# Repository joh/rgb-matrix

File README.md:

# RGB Matrix

RGB Matrix is a driver board for 8x8 RGB matrix displays.

## Features
* USB: The display is controlled over USB.
* 48-bit: Each RGB channel is 16 bits, meaning true 48-bit color!
* Tileable: Multiple displays can be tiled to form bigger displays.
* CA/CC: Both Common Anode and Common Cathode displays are supported.
* Power options: The display can either be powered by USB or via an external
  power adapter.

## Tiling
Several boards can be tiled together to create larger displays. Frames are
propagated to each board over SPI in a daisy chain configuration.

More exotic configurations are also possible:

## 48-bit color
Each color channel is 16 bits which means true 48-bit color per pixel.
That's more than 281 *trillion* colors!
With such a high color depth, transitions between colors appears seamless,
resulting in beautiful smooth animations.

## Hardware
For details about the hardware, head over to [hardware/README.md](hardware/README.md)

## Firmware
TBD

## Client
TBD

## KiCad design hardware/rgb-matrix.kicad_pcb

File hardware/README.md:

# Hardware
The board is based around an STM32F405 microcontroller which drives each LED
with 16-bit hardware PWM. It also handles USB, SPI, etc.

Each column is driven by SN74AC244 buffers, while the rows are driven by
TBD62783 (common anode) or TBD62083/ULN2803A (common cathode).

## PCB
The PCB is 4 layers and connects with the LED matrix like a backpack.

The PCB was designed to handle currents up to 6A, which typically means max 8
panels in series, with the limiting component being the pin headers.

## BOM
TODO

## Assembly
TODO: Some tips on soldering the board

## Common cathode / common anode
TODO: info on components for CA/CC + jumpers

## Power options
TODO: info about the jumpers

## Tiling
TODO: how to set jumpers

## Supported RGB displays
The board was originally designed for the 8x8 RGB Matrix sold by SparkFun (now
sadly discontinued). Luckily there are plenty of displays on the market which
are pin compatible. Some of them are listed below.

Any display with the same form factor should work, *as long as the rows are on
pins 7-10 and 23-26*. Exactly which rows and columns are where is less
important: they can be easily remapped in firmware.

TODO: picture

If you find a display that looks compatible which is not in the list below,
please let me know so I can add it!

Tested displays:
* [YSM-2388CRGBC](https://www.sparkfun.com/products/retired/683) (common cathode, retired)
* [ARK-SZ912388RGB](https://wxjsinfo.en.alibaba.com/product/1877395129-801004755/8x8_RGB_led_matrix_with_7_62mm_pitch.html) (common anode)

Should work:
* [Betlux BL-M23B881RGB-11](http://shop.evilmadscientist.com/productsmenu/241) (common cathode)
* [LEDM88RGBCC](http://www.futurlec.com/LED/LEDM88RGBCC.shtml) (common cathode)

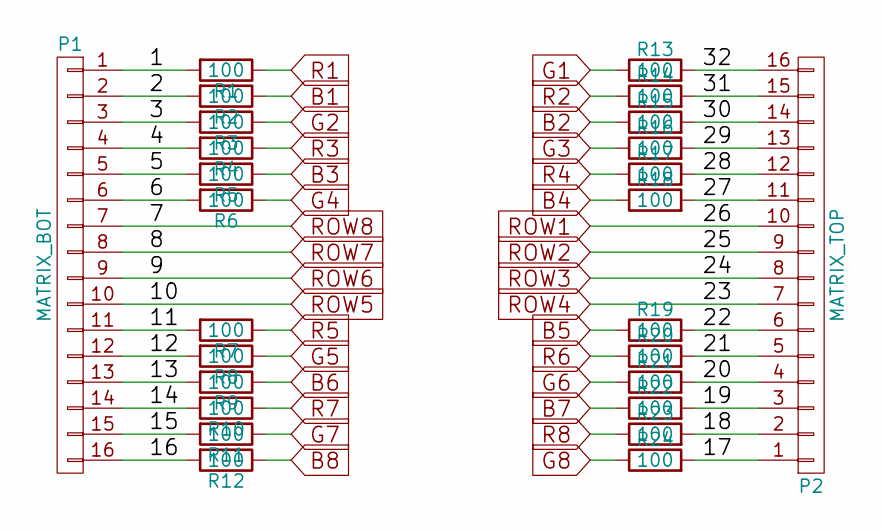
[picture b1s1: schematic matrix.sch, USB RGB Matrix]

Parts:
P1: MATRIX_BOT; Socket_Strip_Straight_1x16
P2: MATRIX_TOP; Socket_Strip_Straight_1x16
R1, R2, R3, R4, R5, R6, R7, R8, R9, R10, R11, R12, R13, R14, R15, R16, R17, R18, R19, R20, R21, R22, R23, R24: 100; R_0805

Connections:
/matrix/1: P1.1, R1.2
/matrix/2: P1.2, R2.2
/matrix/3: P1.3, R3.2
/matrix/4: P1.4, R4.2
/matrix/5: P1.5, R5.2
/matrix/6: P1.6, R6.2
/matrix/11: P1.11, R7.2
/matrix/12: P1.12, R8.2
/matrix/13: P1.13, R9.2
/matrix/14: P1.14, R10.2
/matrix/15: P1.15, R11.2
/matrix/16: P1.16, R12.2
/matrix/17: P2.1, R24.2
/matrix/18: P2.2, R23.2
/matrix/19: P2.3, R22.2
/matrix/20: P2.4, R21.2
/matrix/21: P2.5, R20.2
/matrix/22: P2.6, R19.2
/matrix/27: P2.11, R18.2
/matrix/28: P2.12, R17.2
/matrix/29: P2.13, R16.2
/matrix/30: P2.14, R15.2
/matrix/31: P2.15, R14.2
/matrix/32: P2.16, R13.2
B1: R2.1; also elsewhere on the board
B2: R15.1; also elsewhere on the board
B3: R5.1; also elsewhere on the board
B4: R18.1; also elsewhere on the board
B5: R19.1; also elsewhere on the board
B6: R9.1; also elsewhere on the board
B7: R22.1; also elsewhere on the board
B8: R12.1; also elsewhere on the board
G1: R13.1; also elsewhere on the board
G2: R3.1; also elsewhere on the board
G3: R16.1; also elsewhere on the board
G4: R6.1; also elsewhere on the board
G5: R8.1; also elsewhere on the board
G6: R21.1; also elsewhere on the board
G7: R11.1; also elsewhere on the board
G8: R24.1; also elsewhere on the board
R1: R1.1; also elsewhere on the board
R2: R14.1; also elsewhere on the board
R3: R4.1; also elsewhere on the board
R4: R17.1; also elsewhere on the board
R5: R7.1; also elsewhere on the board
R6: R20.1; also elsewhere on the board
R7: R10.1; also elsewhere on the board
R8: R23.1; also elsewhere on the board
ROW1: P2.10; also elsewhere on the board
ROW2: P2.9; also elsewhere on the board
ROW3: P2.8; also elsewhere on the board
ROW4: P2.7; also elsewhere on the board
ROW5: P1.10; also elsewhere on the board
ROW6: P1.9; also elsewhere on the board
ROW7: P1.8; also elsewhere on the board
ROW8: P1.7; also elsewhere on the board

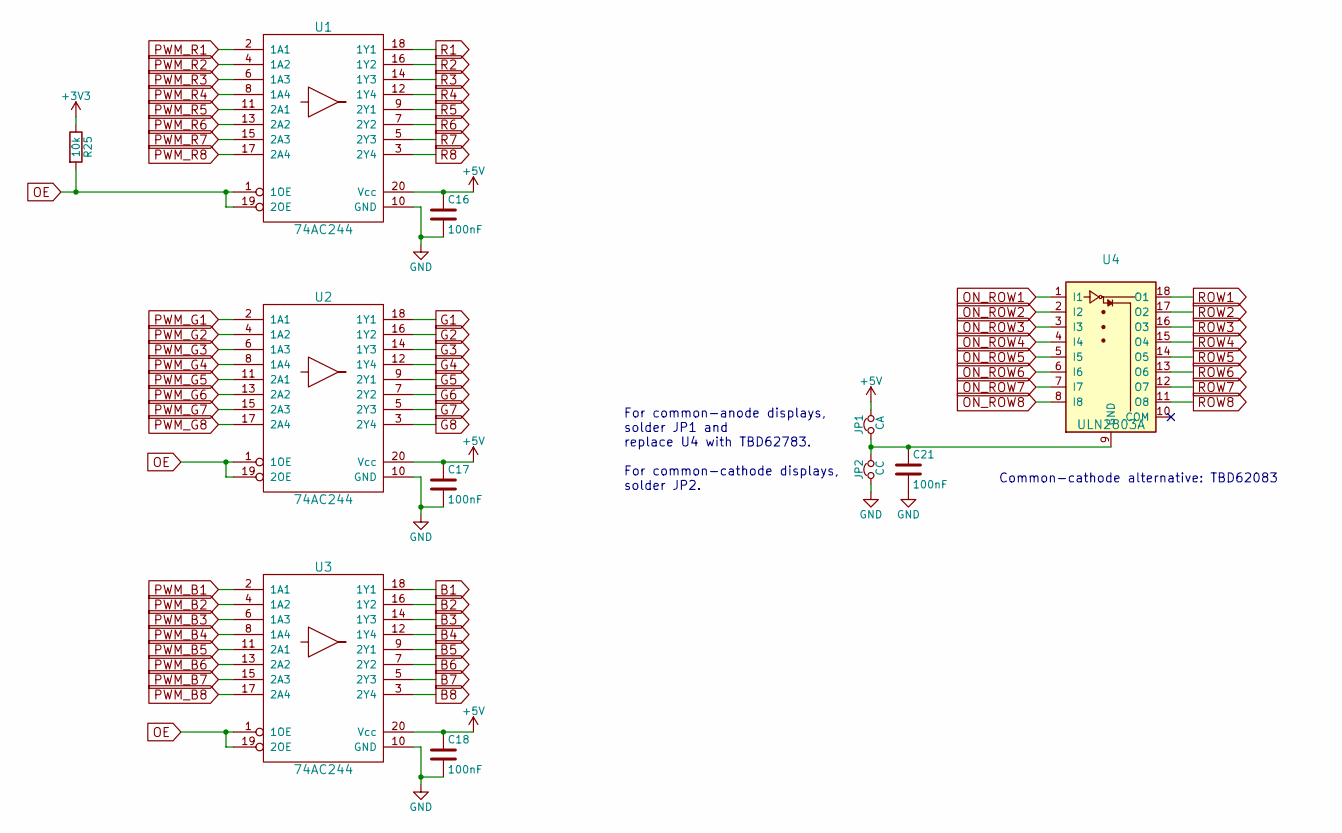
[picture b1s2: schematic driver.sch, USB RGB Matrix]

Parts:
C16, C17, C18, C21: 100nF; C_0805
JP1: CA; SMD-solder-bridge-1mm
JP2: CC; SMD-solder-bridge-1mm
R25: 10k; R_0805
U1, U2, U3: 74AC244; TSSOP-20_4.4x6.5mm_Pitch0.65mm
U4: ULN2803A; SOIC-18W_7.5x11.6mm_Pitch1.27mm

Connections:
+3V3: R25.1; also elsewhere on the board
+5V: C16.1, C17.1, C18.1, JP1.2, U1.20 (Vcc), U2.20 (Vcc), U3.20 (Vcc); also elsewhere on the board
B1: U3.18 (1Y1); also elsewhere on the board
B2: U3.16 (1Y2); also elsewhere on the board
B3: U3.14 (1Y3); also elsewhere on the board
B4: U3.12 (1Y4); also elsewhere on the board
B5: U3.9 (2Y1); also elsewhere on the board
B6: U3.7 (2Y2); also elsewhere on the board
B7: U3.5 (2Y3); also elsewhere on the board
B8: U3.3 (2Y4); also elsewhere on the board
G1: U2.18 (1Y1); also elsewhere on the board
G2: U2.16 (1Y2); also elsewhere on the board
G3: U2.14 (1Y3); also elsewhere on the board
G4: U2.12 (1Y4); also elsewhere on the board
G5: U2.9 (2Y1); also elsewhere on the board
G6: U2.7 (2Y2); also elsewhere on the board
G7: U2.5 (2Y3); also elsewhere on the board
G8: U2.3 (2Y4); also elsewhere on the board
GND: C16.2, C17.2, C18.2, C21.2, JP2.1, U1.10 (GND), U2.10 (GND), U3.10 (GND); also elsewhere on the board
unnamed: C21.1, JP1.1, JP2.2, U4.9 (GND)
OE: R25.2, U1.1 (1OE), U1.19 (2OE), U2.1 (1OE), U2.19 (2OE), U3.1 (1OE), U3.19 (2OE); also elsewhere on the board
ON_ROW1: U4.1 (I1); also elsewhere on the board
ON_ROW2: U4.2 (I2); also elsewhere on the board
ON_ROW3: U4.3 (I3); also elsewhere on the board
ON_ROW4: U4.4 (I4); also elsewhere on the board
ON_ROW5: U4.5 (I5); also elsewhere on the board
ON_ROW6: U4.6 (I6); also elsewhere on the board
ON_ROW7: U4.7 (I7); also elsewhere on the board
ON_ROW8: U4.8 (I8); also elsewhere on the board
PWM_B1: U3.2 (1A1); also elsewhere on the board
PWM_B2: U3.4 (1A2); also elsewhere on the board
PWM_B3: U3.6 (1A3); also elsewhere on the board
PWM_B4: U3.8 (1A4); also elsewhere on the board
PWM_B5: U3.11 (2A1); also elsewhere on the board
PWM_B6: U3.13 (2A2); also elsewhere on the board
PWM_B7: U3.15 (2A3); also elsewhere on the board
PWM_B8: U3.17 (2A4); also elsewhere on the board
PWM_G1: U2.2 (1A1); also elsewhere on the board
PWM_G2: U2.4 (1A2); also elsewhere on the board
PWM_G3: U2.6 (1A3); also elsewhere on the board
PWM_G4: U2.8 (1A4); also elsewhere on the board
PWM_G5: U2.11 (2A1); also elsewhere on the board
PWM_G6: U2.13 (2A2); also elsewhere on the board
PWM_G7: U2.15 (2A3); also elsewhere on the board
PWM_G8: U2.17 (2A4); also elsewhere on the board
PWM_R1: U1.2 (1A1); also elsewhere on the board
PWM_R2: U1.4 (1A2); also elsewhere on the board
PWM_R3: U1.6 (1A3); also elsewhere on the board
PWM_R4: U1.8 (1A4); also elsewhere on the board
PWM_R5: U1.11 (2A1); also elsewhere on the board
PWM_R6: U1.13 (2A2); also elsewhere on the board
PWM_R7: U1.15 (2A3); also elsewhere on the board
PWM_R8: U1.17 (2A4); also elsewhere on the board
R1: U1.18 (1Y1); also elsewhere on the board
R2: U1.16 (1Y2); also elsewhere on the board
R3: U1.14 (1Y3); also elsewhere on the board
R4: U1.12 (1Y4); also elsewhere on the board
R5: U1.9 (2Y1); also elsewhere on the board
R6: U1.7 (2Y2); also elsewhere on the board
R7: U1.5 (2Y3); also elsewhere on the board
R8: U1.3 (2Y4); also elsewhere on the board
ROW1: U4.18 (O1); also elsewhere on the board
ROW2: U4.17 (O2); also elsewhere on the board
ROW3: U4.16 (O3); also elsewhere on the board
ROW4: U4.15 (O4); also elsewhere on the board
ROW5: U4.14 (O5); also elsewhere on the board
ROW6: U4.13 (O6); also elsewhere on the board
ROW7: U4.12 (O7); also elsewhere on the board
ROW8: U4.11 (O8); also elsewhere on the board

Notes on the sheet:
Common-cathode alternative: TBD62083
For common-anode displays, solder JP1 and replace U4 with TBD62783. For common-cathode displays, solder JP2.

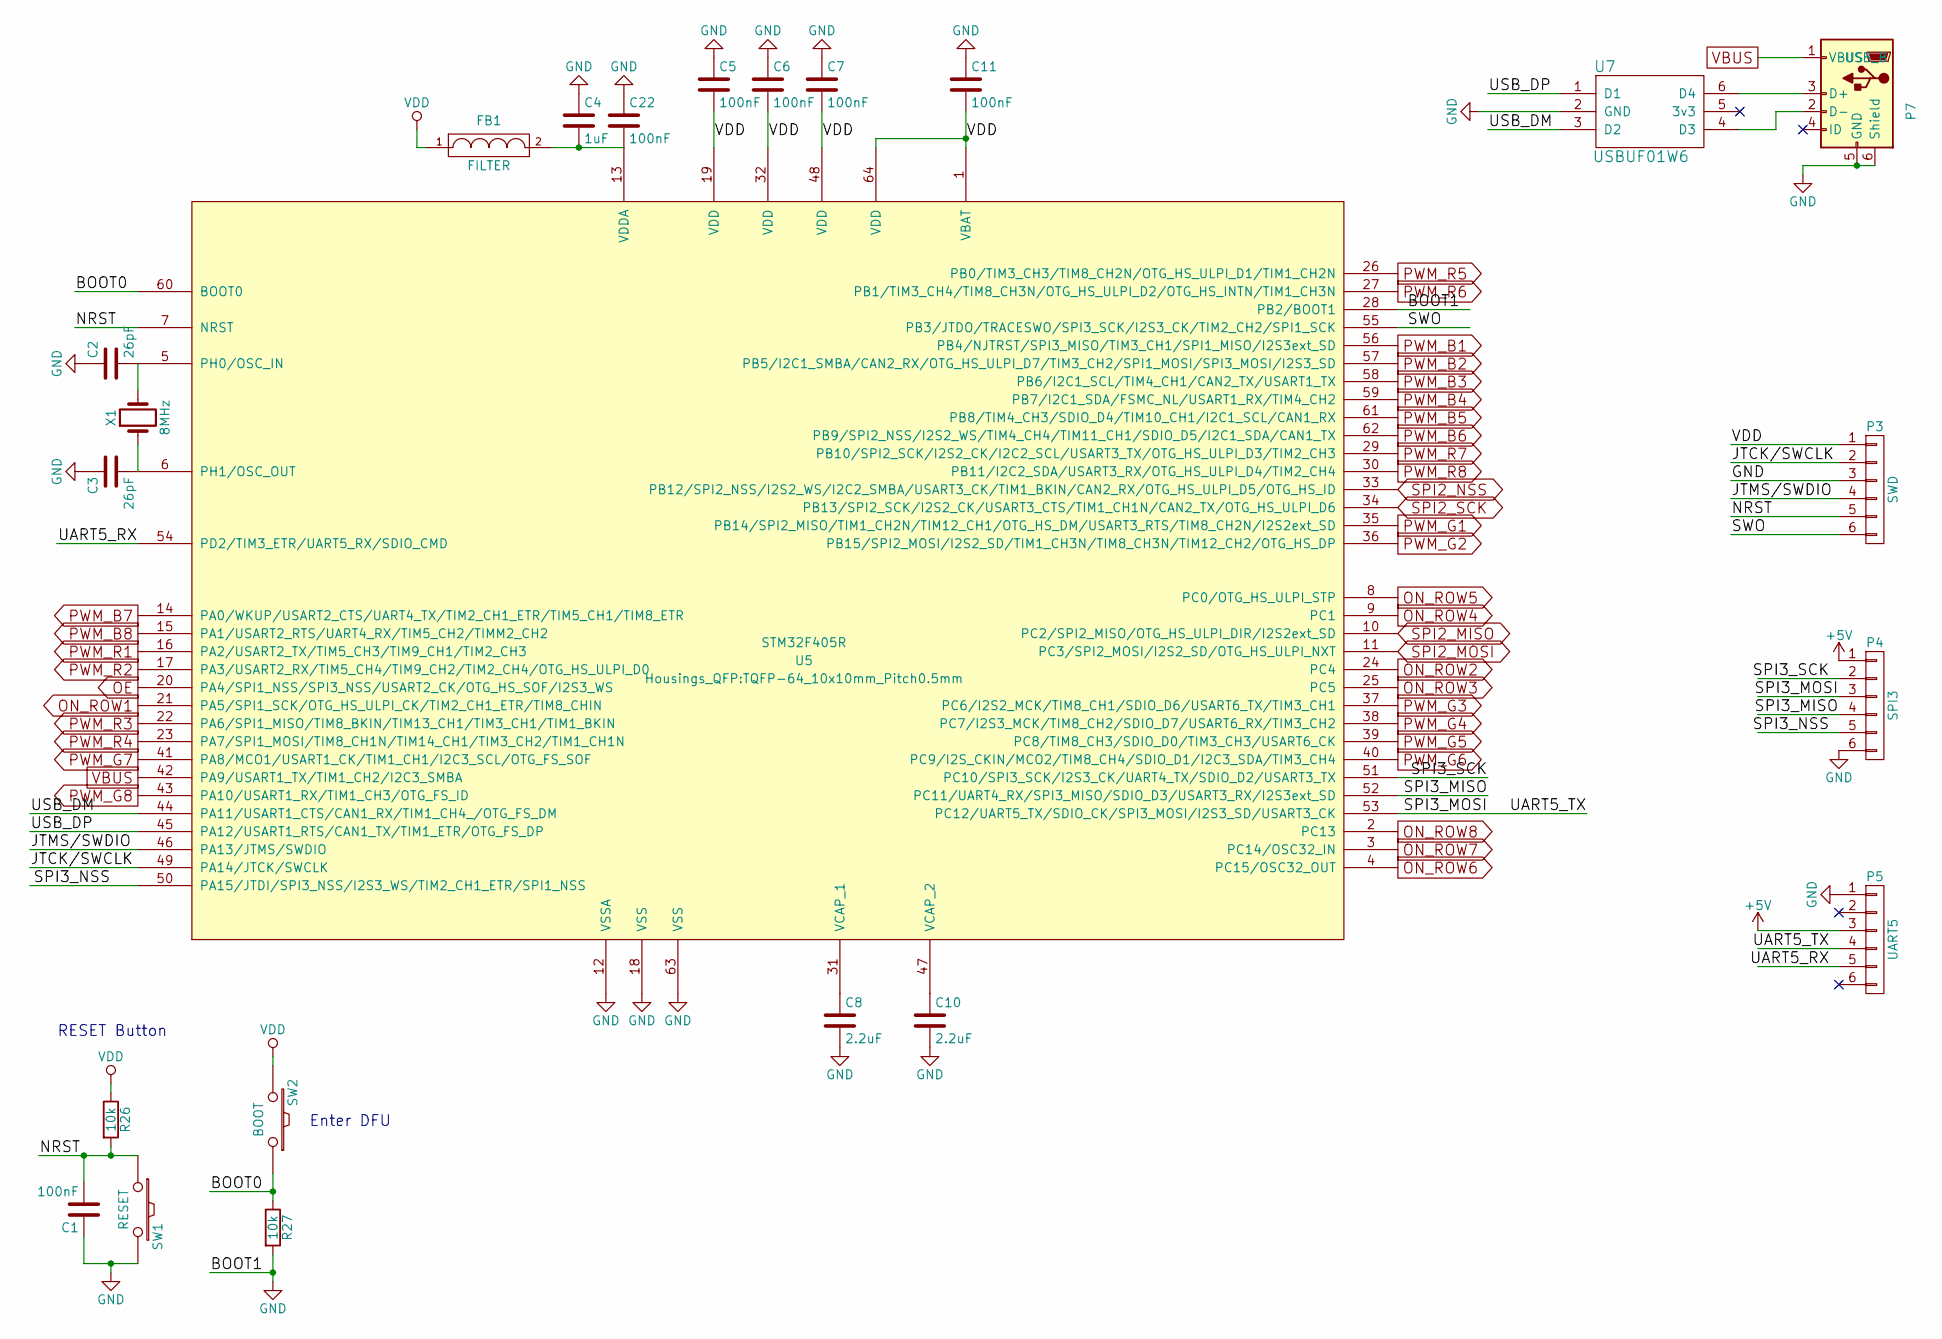
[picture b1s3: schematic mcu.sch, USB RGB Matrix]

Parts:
C1, C5, C6, C7, C11, C22: 100nF; C_0805
C2, C3: 26pF; C_0805
C4: 1uF; C_0805
C8, C10: 2.2uF; C_0805
FB1: FILTER; R_0805
P3: SWD; Pin_Header_Straight_1x06
P4: SPI3; Pin_Header_Straight_1x06
P5: UART5; Pin_Header_Straight_1x06
P7: USB_B; USB_Micro-B
R26, R27: 10k; R_0805
SW1: RESET; SW_SPST_SKQG
SW2: BOOT; SW_SPST_SKQG
U5: STM32F405R; TQFP-64_10x10mm_Pitch0.5mm
U7: USBUF01W6; SOT323-6L
X1: 8MHz; Crystal_SMD_5032_2Pads

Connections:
+3V3: C5.2, C6.2, C7.2, C11.2, FB1.1, P3.1, R26.1, SW2.2, U5.1 (VBAT), U5.19 (VDD), U5.32 (VDD), U5.48 (VDD), U5.64 (VDD); also elsewhere on the board
+5V: P4.1, P5.3; also elsewhere on the board
/mcu/BOOT0: R27.1, SW2.1, U5.60 (BOOT0)
/mcu/JTCK/SWCLK: P3.2, U5.49 (PA14/JTCK/SWCLK)
/mcu/JTMS/SWDIO: P3.4, U5.46 (PA13/JTMS/SWDIO)
/mcu/NRST: C1.2, P3.5, R26.2, SW1.1, U5.7 (NRST)
/mcu/SPI3_MISO: P4.4, U5.52 (PC11/UART4_RX/SPI3_MISO/SDIO_D3/USART3_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)
/mcu/SPI3_MOSI: P4.3, P5.4, U5.53 (PC12/UART5_TX/SDIO_CK/SPI3_MOSI/I2S3_SD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)
/mcu/SPI3_NSS: P4.5, U5.50 (PA15/JTDI/SPI3_NSS/I2S3_WS/TIM2_CH1_ETR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)
/mcu/SPI3_SCK: P4.2, U5.51 (PC10/SPI3_SCK/I2S3_CK/UART4_TX/SDIO_D2/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)
/mcu/SWO: P3.6, U5.55 (PB3/JTDO/TRACESWO/SPI3_SCK/I2S3_CK/TIM2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)
/mcu/UART5_RX: P5.5, U5.54 (PD2/TIM3_ETR/UART5_RX/SDIO_CMD)
/mcu/USB_DM: U5.44 (PA11/USART1_CTS/CAN1_RX/TIM1_CH4_/OTG_F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), U7.3 (D2)
/mcu/USB_DP: U5.45 (PA12/USART1_RTS/CAN1_TX/TIM1_ETR/OTG_FS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), U7.1 (D1)
GND: C1.1, C2.1, C3.1, C4.1, C5.1, C6.1, C7.1, C8.2, C10.2, C11.1, C22.1, P3.3, P4.6, P5.1, P7.5 (GND), P7.6 (Shield), R27.2, SW1.2, U5.12 (VSSA), U5.18 (VSS), U5.28 (PB2/BOOT1), U5.63 (VSS), U7.2 (GND); also elsewhere on the board
unnamed: C2.2, U5.5 (PH0/OSC_IN), X1.2
unnamed: C3.2, U5.6 (PH1/OSC_OUT), X1.1
unnamed: C8.1, U5.31 (VCAP_1)
unnamed: C10.1, U5.47 (VCAP_2)
unnamed: C4.2, C22.2, FB1.2, U5.13 (VDDA)
unnamed: P7.2 (D-), U7.4 (D3)
unnamed: P7.3 (D+), U7.6 (D4)
OE: U5.20 (PA4/SPI1_NSS/SPI3_NSS/USART2_CK/OTG_HS_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); also elsewhere on the board
ON_ROW1: U5.21 (PA5/SPI1_SCK/OTG_HS_ULPI_CK/TIM2_CH1_ET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); also elsewhere on the board
ON_ROW2: U5.24 (PC4); also elsewhere on the board
ON_ROW3: U5.25 (PC5); also elsewhere on the board
ON_ROW4: U5.9 (PC1); also elsewhere on the board
ON_ROW5: U5.8 (PC0/OTG_HS_ULPI_STP); also elsewhere on the board
ON_ROW6: U5.4 (PC15/OSC32_OUT); also elsewhere on the board
ON_ROW7: U5.3 (PC14/OSC32_IN); also elsewhere on the board
ON_ROW8: U5.2 (PC13); also elsewhere on the board
PWM_B1: U5.56 (PB4/NJTRST/SPI3_MISO/TIM3_CH1/SPI1_MISO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); also elsewhere on the board
PWM_B2: U5.57 (PB5/I2C1_SMBA/CAN2_RX/OTG_HS_ULPI_D7/TI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); also elsewhere on the board
PWM_B3: U5.58 (PB6/I2C1_SCL/TIM4_CH1/CAN2_TX/USART1_TX); also elsewhere on the board
PWM_B4: U5.59 (PB7/I2C1_SDA/FSMC_NL/USART1_RX/TIM4_CH2); also elsewhere on the board
PWM_B5: U5.61 (PB8/TIM4_CH3/SDIO_D4/TIM10_CH1/I2C1_SCL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); also elsewhere on the board
PWM_B6: U5.62 (PB9/SPI2_NSS/I2S2_WS/TIM4_CH4/TIM11_CH1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); also elsewhere on the board
PWM_B7: U5.14 (PA0/WKUP/USART2_CTS/UART4_TX/TIM2_CH1_E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); also elsewhere on the board
PWM_B8: U5.15 (PA1/USART2_RTS/UART4_RX/TIM5_CH2/TIMM2_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); also elsewhere on the board
PWM_G1: U5.35 (PB14/SPI2_MISO/TIM1_CH2N/TIM12_CH1/OTG_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); also elsewhere on the board
PWM_G2: U5.36 (PB15/SPI2_MOSI/I2S2_SD/TIM1_CH3N/TIM8_C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); also elsewhere on the board
PWM_G3: U5.37 (PC6/I2S2_MCK/TIM8_CH1/SDIO_D6/USART6_TX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); also elsewhere on the board
PWM_G4: U5.38 (PC7/I2S3_MCK/TIM8_CH2/SDIO_D7/USART6_RX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); also elsewhere on the board
PWM_G5: U5.39 (PC8/TIM8_CH3/SDIO_D0/TIM3_CH3/USART6_CK); also elsewhere on the board
PWM_G6: U5.40 (PC9/I2S_CKIN/MCO2/TIM8_CH4/SDIO_D1/I2C3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); also elsewhere on the board
PWM_G7: U5.41 (PA8/MCO1/USART1_CK/TIM1_CH1/I2C3_SCL/OT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); also elsewhere on the board
PWM_G8: U5.43 (PA10/USART1_RX/TIM1_CH3/OTG_FS_ID); also elsewhere on the board
PWM_R1: U5.16 (PA2/USART2_TX/TIM5_CH3/TIM9_CH1/TIM2_CH3); also elsewhere on the board
PWM_R2: U5.17 (PA3/USART2_RX/TIM5_CH4/TIM9_CH2/TIM2_CH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); also elsewhere on the board
PWM_R3: U5.22 (PA6/SPI1_MISO/TIM8_BKIN/TIM13_CH1/TIM3_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); also elsewhere on the board
PWM_R4: U5.23 (PA7/SPI1_MOSI/TIM8_CH1N/TIM14_CH1/TIM3_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); also elsewhere on the board
PWM_R5: U5.26 (PB0/TIM3_CH3/TIM8_CH2N/OTG_HS_ULPI_D1/T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); also elsewhere on the board
PWM_R6: U5.27 (PB1/TIM3_CH4/TIM8_CH3N/OTG_HS_ULPI_D2/O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); also elsewhere on the board
PWM_R7: U5.29 (PB10/SPI2_SCK/I2S2_CK/I2C2_SCL/USART3_T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); also elsewhere on the board
PWM_R8: U5.30 (PB11/I2C2_SDA/USART3_RX/OTG_HS_ULPI_D4/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); also elsewhere on the board
SPI2_MISO: U5.10 (PC2/SPI2_MISO/OTG_HS_ULPI_DIR/I2S2ext_SD); also elsewhere on the board
SPI2_MOSI: U5.11 (PC3/SPI2_MOSI/I2S2_SD/OTG_HS_ULPI_NXT); also elsewhere on the board
SPI2_NSS: U5.33 (PB12/SPI2_NSS/I2S2_WS/I2C2_SMBA/USART3_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); also elsewhere on the board
SPI2_SCK: U5.34 (PB13/SPI2_SCK/I2S2_CK/USART3_CTS/TIM1_C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); also elsewhere on the board
VBUS: P7.1 (VBUS), U5.42 (PA9/USART1_TX/TIM1_CH2/I2C3_SMBA); also elsewhere on the board

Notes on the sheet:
Enter DFU
RESET Button

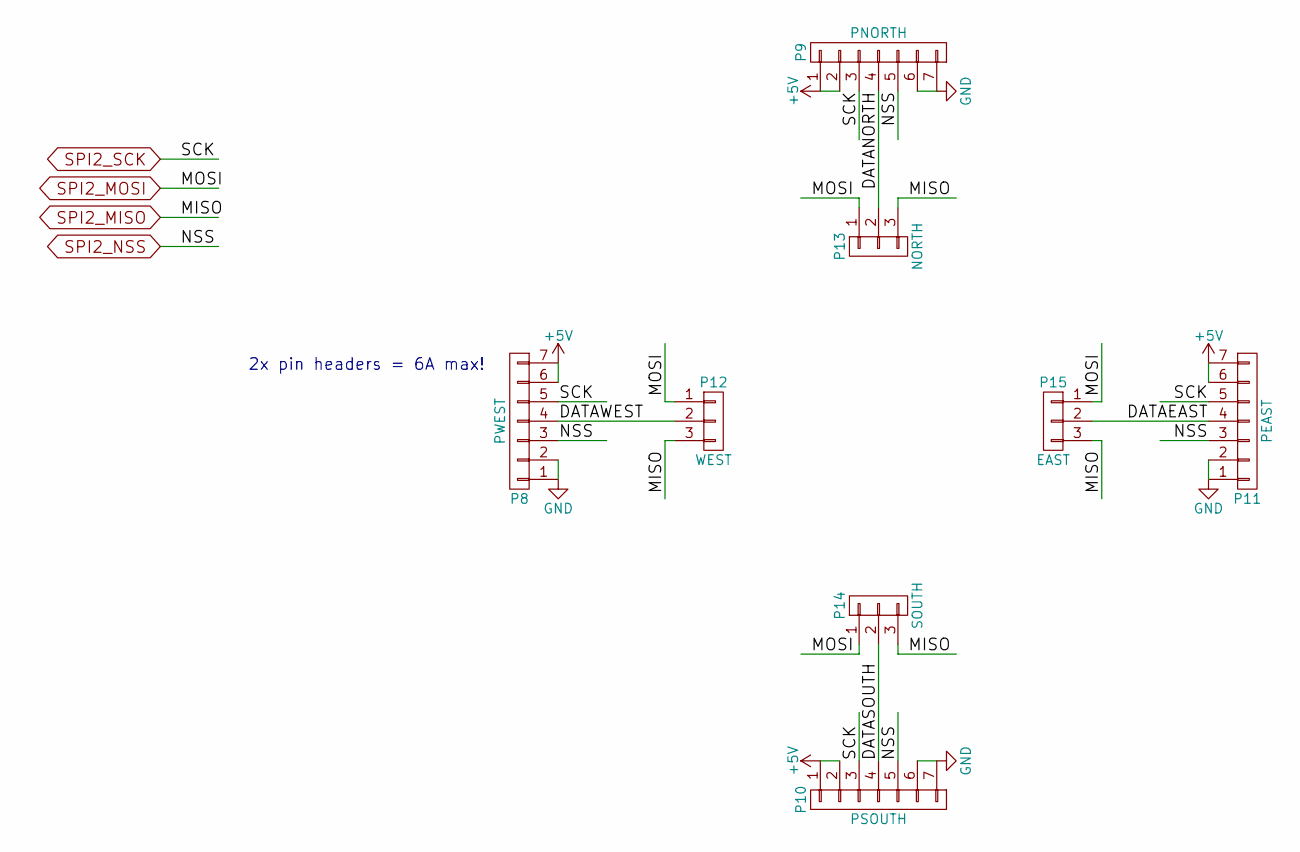
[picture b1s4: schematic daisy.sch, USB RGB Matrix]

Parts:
P8: PWEST; Socket_Strip_Angled_1x07
P9: PNORTH; Pin_Header_Angled_1x07_Pitch2.54mm
P10: PSOUTH; Socket_Strip_Angled_1x07
P11: PEAST; Pin_Header_Angled_1x07_Pitch2.54mm
P12: WEST; Pin_Header_Straight_1x03
P13: NORTH; Pin_Header_Straight_1x03
P14: SOUTH; Pin_Header_Straight_1x03
P15: EAST; Pin_Header_Straight_1x03

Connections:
+5V: P8.6, P8.7, P9.1, P9.2, P10.1, P10.2, P11.6, P11.7; also elsewhere on the board
/daisy/DATAEAST: P11.4, P15.2
/daisy/DATANORTH: P9.4, P13.2
/daisy/DATASOUTH: P10.4, P14.2
/daisy/DATAWEST: P8.4, P12.2
GND: P8.1, P8.2, P9.6, P9.7, P10.6, P10.7, P11.1, P11.2; also elsewhere on the board
SPI2_MISO: P12.3, P13.3, P14.3, P15.3; also elsewhere on the board
SPI2_MOSI: P12.1, P13.1, P14.1, P15.1; also elsewhere on the board
SPI2_NSS: P8.3, P9.5, P10.5, P11.3; also elsewhere on the board
SPI2_SCK: P8.5, P9.3, P10.3, P11.5; also elsewhere on the board

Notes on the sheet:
2x pin headers = 6A max!

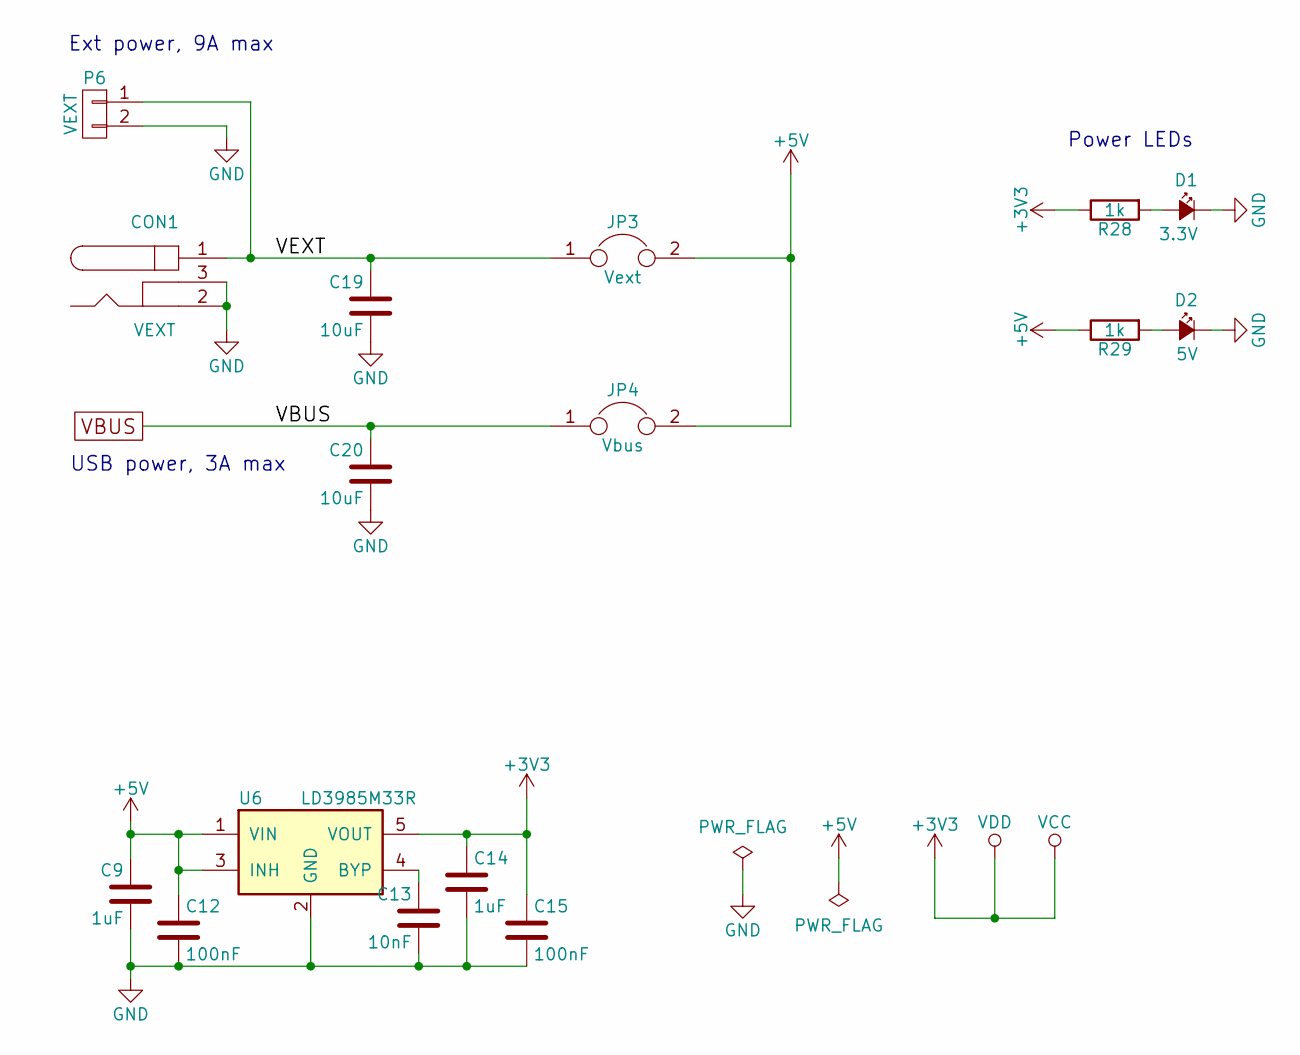
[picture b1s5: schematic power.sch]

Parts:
C9, C14: 1uF; C_0805
C12, C15: 100nF; C_0805
C13: 10nF; C_0805
C19, C20: 10uF; C_0805
CON1: VEXT; BARREL_JACK
D1: 3.3V; LED_1206
D2: 5V; LED_1206
JP3: Vext; SMD-solder-bridge-3mm
JP4: Vbus; SMD-solder-bridge-3mm
P6: VEXT; Pin_Header_Straight_1x02_Pitch2.54mm
R28, R29: 1k; R_0805
U6: LD3985M33R; SOT-23-5

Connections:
+3V3: C14.1, C15.1, R28.1, U6.5 (VOUT); also elsewhere on the board
+5V: C9.1, C12.1, JP3.2, JP4.2, R29.1, U6.1 (VIN), U6.3 (INH); also elsewhere on the board
/power/VEXT: C19.1, CON1.1, JP3.1, P6.1
GND: C9.2, C12.2, C13.2, C14.2, C15.2, C19.2, C20.2, CON1.2, CON1.3, D1.1 (K), D2.1 (K), P6.2, U6.2 (GND); also elsewhere on the board
unnamed: C13.1, U6.4 (BYP)
unnamed: D1.2 (A), R28.2
unnamed: D2.2 (A), R29.2
VBUS: C20.1, JP4.1; also elsewhere on the board

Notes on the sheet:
Ext power, 9A max
USB power, 3A max
Power LEDs

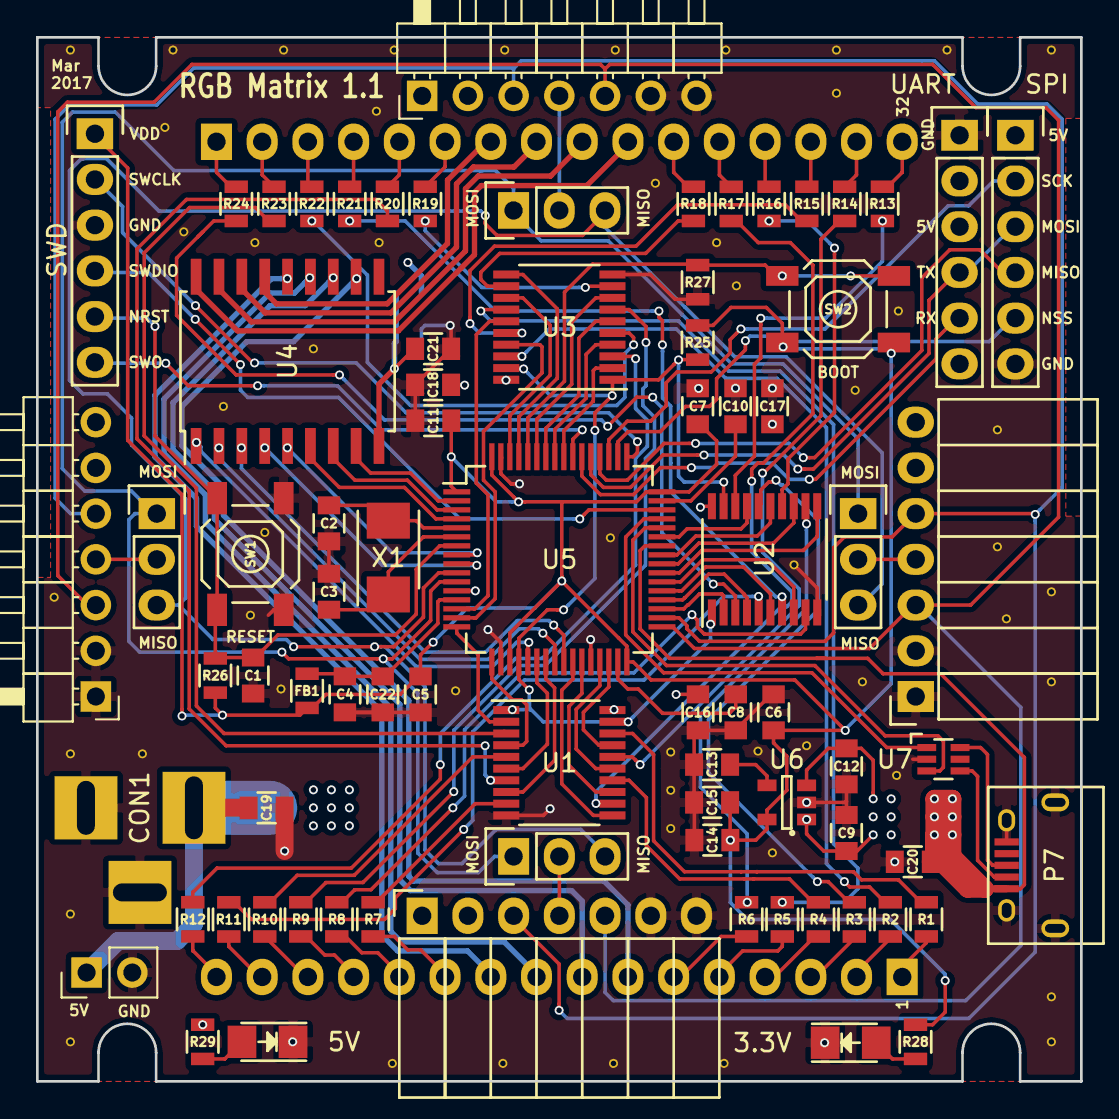
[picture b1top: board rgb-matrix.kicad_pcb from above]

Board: 4 copper layers, 58.0 x 58.0 mm, 84 parts (0 on the bottom side), 125 nets.

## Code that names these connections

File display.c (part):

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};

static struct gpio row_gpios[] = {
    {GPIOA, GPIO5},  // ON_ROW1
    {GPIOC, GPIO4},  // ON_ROW2
    {GPIOC, GPIO5},  // ON_ROW3
    {GPIOC, GPIO1},  // ON_ROW4
    {GPIOC, GPIO0},  // ON_ROW5
    {GPIOC, GPIO15}, // ON_ROW6
    {GPIOC, GPIO14}, // ON_ROW7
    {GPIOC, GPIO13}, // ON_ROW8
};

/*
 * Columns
 */
static __IO uint32_t *red[8] = {
    &TIM5_CCR3,  // R1, PA2,  TIM5_CH3
    &TIM5_CCR4,  // R2, PA3,  TIM5_CH4
    &TIM13_CCR1, // R3, PA6,  TIM13_CH1
    &TIM14_CCR1, // R4, PA7,  TIM14_CH1
    &TIM3_CCR3,  // R5, PB0,  TIM3_CH3
    &TIM3_CCR4,  // R6, PB1,  TIM3_CH4
    &TIM2_CCR3,  // R7, PB10, TIM2_CH3
    &TIM2_CCR4,  // R8, PB11, TIM2_CH4
};

static __IO uint32_t *green[8] = {
    &TIM12_CCR1, // G1, PB14, TIM12_CH1
    &TIM12_CCR2, // G2, PB15, TIM12_CH2
    &TIM8_CCR1,  // G3, PC6,  TIM8_CH1
    &TIM8_CCR2,  // G4, PC7,  TIM8_CH2
    &TIM8_CCR3,  // G5, PC8,  TIM8_CH3
    &TIM8_CCR4,  // G6, PC9,  TIM8_CH4
    &TIM1_CCR1,  // G7, PA8,  TIM1_CH1
    &TIM1_CCR3,  // G8, PA10, TIM1_CH3
};

static __IO uint32_t *blue[8] = {
    &TIM3_CCR1, // B1, PB4, TIM3_CH1
    &TIM3_CCR2, // B2, PB5, TIM3_CH2
    &TIM4_CCR1, // B3, PB6, TIM4_CH1
    &TIM4_CCR2, // B4, PB7, TIM4_CH2
    &TIM4_CCR3, // B5, PB8, TIM4_CH3
    &TIM4_CCR4, // B6, PB9, TIM4_CH4
    &TIM5_CCR1, // B7, PA0, TIM5_CH1
    &TIM5_CCR2, // B8, PA1, TIM5_CH2
};


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     * Columns
     */

    /* PA0,1,2,3: TIM5_CH1,2,3,4 */
    gpios = GPIO0 | GPIO1 | GPIO2 | GPIO3;
    gpio_mode_setup(GPIOA, GPIO_MODE_AF, GPIO_PUPD_NONE, gpios);
    gpio_set_af(GPIOA, GPIO_AF2, gpios);

    /* PA6,7: TIM13_CH1, TIM14_CH1 */
    gpios = GPIO6 | GPIO7;
    gpio_mode_setup(GPIOA, GPIO_MODE_AF, GPIO_PUPD_NONE, gpios);
    gpio_set_af(GPIOA, GPIO_AF9, gpios);

    /* PA8,10: TIM1_CH1,3 */
    gpios = GPIO8 | GPIO10;
    gpio_mode_setup(GPIOA, GPIO_MODE_AF, GPIO_PUPD_NONE, gpios);
    gpio_set_af(GPIOA, GPIO_AF1, gpios);

    /* PB0,1,4,5: TIM3_CH3,4,1,2 */
    gpios = GPIO0 | GPIO1 | GPIO4 | GPIO5;
    gpio_mode_setup(GPIOB, GPIO_MODE_AF, GPIO_PUPD_NONE, gpios);
    gpio_set_af(GPIOB, GPIO_AF2, gpios);

    /* PB6,7,8,9: TIM4_CH1,2,3,4 */
    gpios = GPIO6 | GPIO7 | GPIO8 | GPIO9;
    gpio_mode_setup(GPIOB, GPIO_MODE_AF, GPIO_PUPD_NONE, gpios);
    gpio_set_af(GPIOB, GPIO_AF2, gpios);

    /* PB10,11: TIM2_CH3,4 */
    gpios = GPIO10 | GPIO11;
    gpio_mode_setup(GPIOB, GPIO_MODE_AF, GPIO_PUPD_NONE, gpios);
    gpio_set_af(GPIOB, GPIO_AF1, gpios);

    /* PB14,15: TIM12_CH1,2 */
    gpios = GPIO14 | GPIO15;
    gpio_mode_setup(GPIOB, GPIO_MODE_AF, GPIO_PUPD_NONE, gpios);
    gpio_set_af(GPIOB, GPIO_AF9, gpios);

    /* PC6,7,8,9: TIM8_CH1,2,3,4 */
    gpios = GPIO6 | GPIO7 | GPIO8 | GPIO9;
    gpio_mode_setup(GPIOC, GPIO_MODE_AF, GPIO_PUPD_NONE, gpios);
    gpio_set_af(GPIOC, GPIO_AF3, gpios);
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    /*gpio_set_output_options(GPIOC, GPIO_OTYPE_PP, GPIO_OSPEED_100MHZ,*/
            /*GPIO10 | GPIO11 | GPIO12);*/

    // PA4: OE
    gpio_mode_setup(GPIOA, GPIO_MODE_OUTPUT, GPIO_PUPD_NONE, GPIO4);
}

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
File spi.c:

#include <stdio.h>
#include <libopencmsis/core_cm3.h>
#include <libopencm3/stm32/spi.h>
#include <libopencm3/stm32/rcc.h>
#include <libopencm3/stm32/gpio.h>
#include <libopencm3/stm32/exti.h>
#include <libopencm3/cm3/nvic.h>
#include <libopencm3/stm32/syscfg.h>

#include "spi.h"
#include "display.h"
#include "utils.h"

static volatile uint8_t spi_bytes_rcvd = 0;

/* Write position display backbuffer */
static __IO unsigned int dispbuf_pos = 0;

/* Whether we're master or slave in the daisy chain */
static bool daisy_is_master = false;

/* IRQ on SPI2_NSS/SPI3_NSS rising edge */
void exti15_10_isr(void)
{
    exti_reset_request(EXTI15 | EXTI12);
    /* Signal swapbuffers. The display code will
     * call spi_daisy_swapbuffers() when complete. */
    display_swapbuffers_nowait();
    dispbuf_pos = 0;
}

/* Called right after swapbuffers is done */
void spi_daisy_swapbuffers(void)
{
    if (daisy_is_master)
        return;

    uint8_t *dispbuf = (uint8_t *)display_get_backbuffer();

    /* Slaves in the daisy chain need to prepare the TX buffer so it's ready
     * when the first byte is clocked in to the RX buffer. Fill the TX buffer
     * with the first byte to be overwritten in the framebuffer */
    spi_daisy_write(dispbuf[0]);
}

/* SPI slave */
void spi3_isr(void)
{
    uint8_t *dispbuf = (uint8_t *)display_get_backbuffer();
    uint8_t byte = SPI_DR(SPI3);

    /* Fill framebuffer with received byte */
    dispbuf[dispbuf_pos] = byte;
    dispbuf_pos = (dispbuf_pos + 1) % sizeof(DisplayBuf);

    /* Forward next (oldest) byte in framebuffer to the daisy chain */
    spi_daisy_write(dispbuf[dispbuf_pos]);

    /* Prepare next (oldest) byte in the framebuffer for the next transmission */
    SPI_DR(SPI3) = dispbuf[dispbuf_pos];
}

/* Daisy slave */
void spi2_isr(void)
{
    uint8_t *dispbuf = (uint8_t *)display_get_backbuffer();
    uint8_t byte = SPI_DR(SPI2);

    /* Fill framebuffer with received byte */
    dispbuf[dispbuf_pos] = byte;
    dispbuf_pos = (dispbuf_pos + 1) % sizeof(DisplayBuf);

    /* Prepare next (oldest) byte in the framebuffer for the next transmission */
    SPI_DR(SPI2) = dispbuf[dispbuf_pos];
}

void spi_daisy_init_master()
{
    uint16_t gpios = 0;

    spi_disable(SPI2);

    spi_set_master_mode(SPI2);
    spi_set_baudrate_prescaler(SPI2, 7); // TODO: increase once debug phase is over
    spi_enable_ss_output(SPI2);

    /* PB12: SPI2_NSS (controlled by master) */
    gpios = GPIO12;
    gpio_mode_setup(GPIOB, GPIO_MODE_OUTPUT, GPIO_PUPD_NONE, gpios);
    spi_daisy_set_nss_low();

    /* Don't need interrupts in master mode */
    nvic_disable_irq(NVIC_SPI2_IRQ);
    spi_disable_rx_buffer_not_empty_interrupt(SPI2);

    exti_disable_request(EXTI12);

    spi_enable(SPI2);

    daisy_is_master = true;
}

void spi_daisy_init_slave()
{
    uint16_t gpios = 0;

    spi_disable(SPI2);

    spi_set_slave_mode(SPI2);

    nvic_enable_irq(NVIC_SPI2_IRQ);
    spi_enable_rx_buffer_not_empty_interrupt(SPI2);

    /* PB12: SPI2_NSS (NSS input in slave mode) */
    gpios = GPIO12;
    gpio_mode_setup(GPIOB, GPIO_MODE_AF, GPIO_PUPD_NONE, gpios);
    gpio_set_af(GPIOB, GPIO_AF5, gpios);

    /* Configure interrupt on rising edge of SPI2_NSS */
    nvic_enable_irq(NVIC_EXTI15_10_IRQ);
    exti_select_source(EXTI12, GPIOB);
    exti_set_trigger(EXTI12, EXTI_TRIGGER_RISING);
    exti_enable_request(EXTI12);

    spi_enable(SPI2);

    daisy_is_master = false;
}

void spi_daisy_set_nss_low()
{
    gpio_clear(GPIOB, GPIO12);
}

void spi_daisy_set_nss_high()
{
    /* Wait for any pending transmission to complete */
    while (!(SPI_SR(SPI2) & SPI_SR_TXE));
    while ((SPI_SR(SPI2) & SPI_SR_BSY));
    /* TODO: Sleep needed when testing with the BusPirate spisniffer.
     * Check if needed with daisy chain device at full speed */
    usleep(10);

    gpio_set(GPIOB, GPIO12);
}

void spi_daisy_send(uint16_t data)
{
    spi_send(SPI2, data);
}

/* Non-blocking */
void spi_daisy_write(uint16_t data)
{
    spi_write(SPI2, data);
}

bool spi_daisy_is_master(void)
{
    return daisy_is_master;
}

void spi_daisy_init()
{
    uint16_t gpios = 0;

    rcc_periph_clock_enable(RCC_GPIOB);
    rcc_periph_clock_enable(RCC_GPIOC);
    rcc_periph_clock_enable(RCC_SYSCFG);
    rcc_periph_clock_enable(RCC_SPI2);

    /* PB13: SPI2_SCK */
    gpios = GPIO13;
    gpio_mode_setup(GPIOB, GPIO_MODE_AF, GPIO_PUPD_NONE, gpios);
    gpio_set_af(GPIOB, GPIO_AF5, gpios);

    /* PC2,3: SPI2_{MISO,MOSI} */
    gpios = GPIO2 | GPIO3;
    gpio_mode_setup(GPIOC, GPIO_MODE_AF, GPIO_PUPD_NONE, gpios);
    gpio_set_af(GPIOC, GPIO_AF5, gpios);

    /* Common SPI stuff */
    spi_set_standard_mode(SPI2, 0); // Sets CPOL, CPHA
    spi_set_dff_8bit(SPI2);
    spi_send_msb_first(SPI2);

    /* Set slave mode by default */
    spi_daisy_init_slave();
}

void spi_slave_init()
{
    uint16_t gpios = 0;

    rcc_periph_clock_enable(RCC_GPIOA);
    rcc_periph_clock_enable(RCC_GPIOC);
    rcc_periph_clock_enable(RCC_SYSCFG);
    rcc_periph_clock_enable(RCC_SPI3);

    /* PC10,11,12: SPI3_{SCK,MISO,MOSI} */
    gpios = GPIO10 | GPIO11 | GPIO12;
    gpio_mode_setup(GPIOC, GPIO_MODE_AF, GPIO_PUPD_NONE, gpios);
    gpio_set_af(GPIOC, GPIO_AF6, gpios);

    /* PA15: SPI3_NSS */
    gpios = GPIO15;
    gpio_mode_setup(GPIOA, GPIO_MODE_AF, GPIO_PUPD_NONE, gpios);
    gpio_set_af(GPIOA, GPIO_AF6, gpios);

    /* Configure interrupt on rising edge of SPI3_NSS */
    nvic_enable_irq(NVIC_EXTI15_10_IRQ);
    exti_select_source(EXTI15, GPIOA);
    exti_set_trigger(EXTI15, EXTI_TRIGGER_RISING);
    exti_enable_request(EXTI15);

    /* Configure SPI slave */
    spi_set_dff_8bit(SPI3);
    spi_set_standard_mode(SPI3, 0); // Sets CPOL, CPHA
    spi_send_msb_first(SPI3);
    spi_set_slave_mode(SPI3);

    /* Enable SPI interrupts */
    nvic_enable_irq(NVIC_SPI3_IRQ);
    spi_enable_rx_buffer_not_empty_interrupt(SPI3);

    spi_enable(SPI3);
}

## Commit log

2012-07-02 Initial tests: single row, red pixels only
2012-08-18 Rows enabled, working (red) matrix display
2012-08-18 Timer-based row multiplexing
2015-12-15 Port to libopencm3 :)
2016-02-14 All colors :)
2016-02-14 Use TIM9 instead of TIM13 and TIM14
2016-05-01 Cleanup unused code
2016-05-03 Major code rework, display vsync, lots of tests!
2016-05-03 Add missing makefiles and ldscript
2016-05-03 Ignore some files
2016-11-03 Add test_columns() and test_rows()
2017-01-08 Initial version with schottky diodes for power
2017-01-11 LTC4417 for automatic power source switching
2017-01-12 Assign footprints
2017-01-12 Fix IRF7324 footprint
2017-01-18 Preliminary routing with LTC4417
2017-01-18 Probably not enough space for LTC4417
2017-01-19 Remove LTC4417, replace with solder bridges
    Simply not enough space on the board!
2017-01-19 Completely routed PCB!
2017-01-20 Fix silkscreen
2017-01-22 Add 2nd GND pin for more curent + minor changes
2017-01-22 Add more margin for the board to board connectors
2017-01-22 Cleanup tracks, fix 3d models
2017-01-22 Place vias on pads
2017-01-22 PCB tweaking #1
2017-01-25 Fix footprint for U7, minor other fixes
2017-01-25 Fixup silkscreen
2017-01-26 Add GND pour to Top and Bottom + via stiching
2017-01-26 Add more datasheets
2017-01-26 Add silk: name and URL
2017-01-27 Add silk art, minor fixes
2017-02-01 Change pushbutton part
2017-02-19 USB main loop, semihosting debugging
2017-02-21 Fix solder mask clearance
    Reduce clearance to 0.05mm so there is solder mask between all pads!
2017-02-25 Add test_white()
2017-02-25 Pull OE low to enable columns
2017-02-26 Fix pulse width issues with timers
    Don't use one_shot, which doesn't allow us to disable outputs quickly on
    overflow. Instead use continuous timers and preload OCR registers with
    zero to disable all outputs while in the ISR.
2017-02-26 Add white to test_fade()
2017-02-28 Forgot to add usb.c!
2017-03-13 Working SPI daisy chain + slave!
2017-03-13 Improve semihosting build support
    Enabled with make DEBUG=1
    Start openocd console with make console
2017-03-13 Add support for setting clear color via USB
2017-03-16 Update component versions (ULN2308A and USB_B)
2017-03-16 Disconnect pullup from USBUF
    STM32 has internal pullups
2017-03-16 PCB fixes for 1.1
    * Disconnect DATA lines in daisy chain
    * Fix barrel jack footprint (hole size)
    * Fix some 3D models
    * Update PCB netlist
2017-03-17 Add support for common anode displays
2017-03-17 Simplify test_white()
2017-03-26 Move firmware to subdirectory
    Remove old unused files from before libopencm3
2017-03-26 Add define for data ep addr
2017-03-26 Add rudimentary python client
2017-03-27 Enable pullups on NSS lines
    Prevents spurious interrupts when touching pins etc
2017-04-15 Add some unit tests
    Mostly replicates the firmware tests
2017-04-17 Add frame and layout stuff
2017-04-17 Increase SPI speed to ~1.3MHz
2017-04-17 Make tests layout-aware
2017-04-17 Make layout global argument for CLI
2017-04-17 Add text and random commands to CLI
2017-04-19 Add comment about SPI clock limitation
2017-04-20 Add image loading functionality
    Including gif animations!
2017-04-20 Add gamma correction
2017-04-20 Add brightness adjustment
2017-04-20 Add screencast feature
    Requires GNOME shell...
2017-06-14 Bump schematic version to 1.1
2017-06-14 python3 fixes
2017-10-03 Print usage if no command is given
2017-10-03 Remove unused rescue library
2017-10-03 Fix 3D model names
2017-10-14 Add README (work in progress)
2017-10-15 Add some images of the PCB: bare and assembled
2017-10-16 Use DMA for SPI daisy chain
2018-01-11 Update libopencm3 path, set common anode as default
2018-01-14 Add multiple backends to client (USB and SPI)
2018-01-17 Move SPI daisy chain code to spi-daisy.[ch]
2018-01-30 Add SWO trace support
    Get rid of semihosting (slow) and use SWO trace instead
2018-02-04 DMA for SPI slave interface
2018-02-04 Update SPI client to new interface
2018-02-04 Use env var for backend in tests
2018-02-10 Become daisy master on first spi message
2018-02-12 Add resize argument for image
2023-12-18 Convert frames to RGB before resizing
    Otherwise the quality is degraded for the first frame of some GIFs
